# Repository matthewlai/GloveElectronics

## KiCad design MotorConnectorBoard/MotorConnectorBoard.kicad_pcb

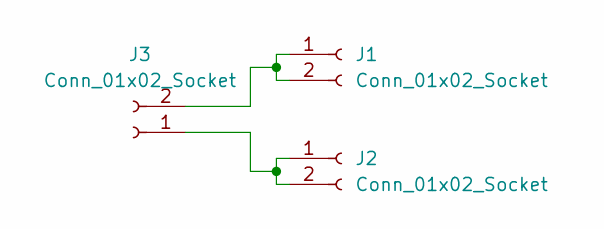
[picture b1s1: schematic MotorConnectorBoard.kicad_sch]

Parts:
J1, J2: Conn_01x02_Socket; PinHeader_1x02_P2.54mm_Vertical
J3: Conn_01x02_Socket; VLV101040A

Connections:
unnamed: J1.1, J1.2, J3.2
unnamed: J2.1, J2.2, J3.1

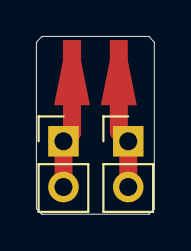
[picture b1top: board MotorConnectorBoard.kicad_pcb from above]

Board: 2 copper layers, 6.6 x 9.9 mm, 3 parts (0 on the bottom side), 2 nets.

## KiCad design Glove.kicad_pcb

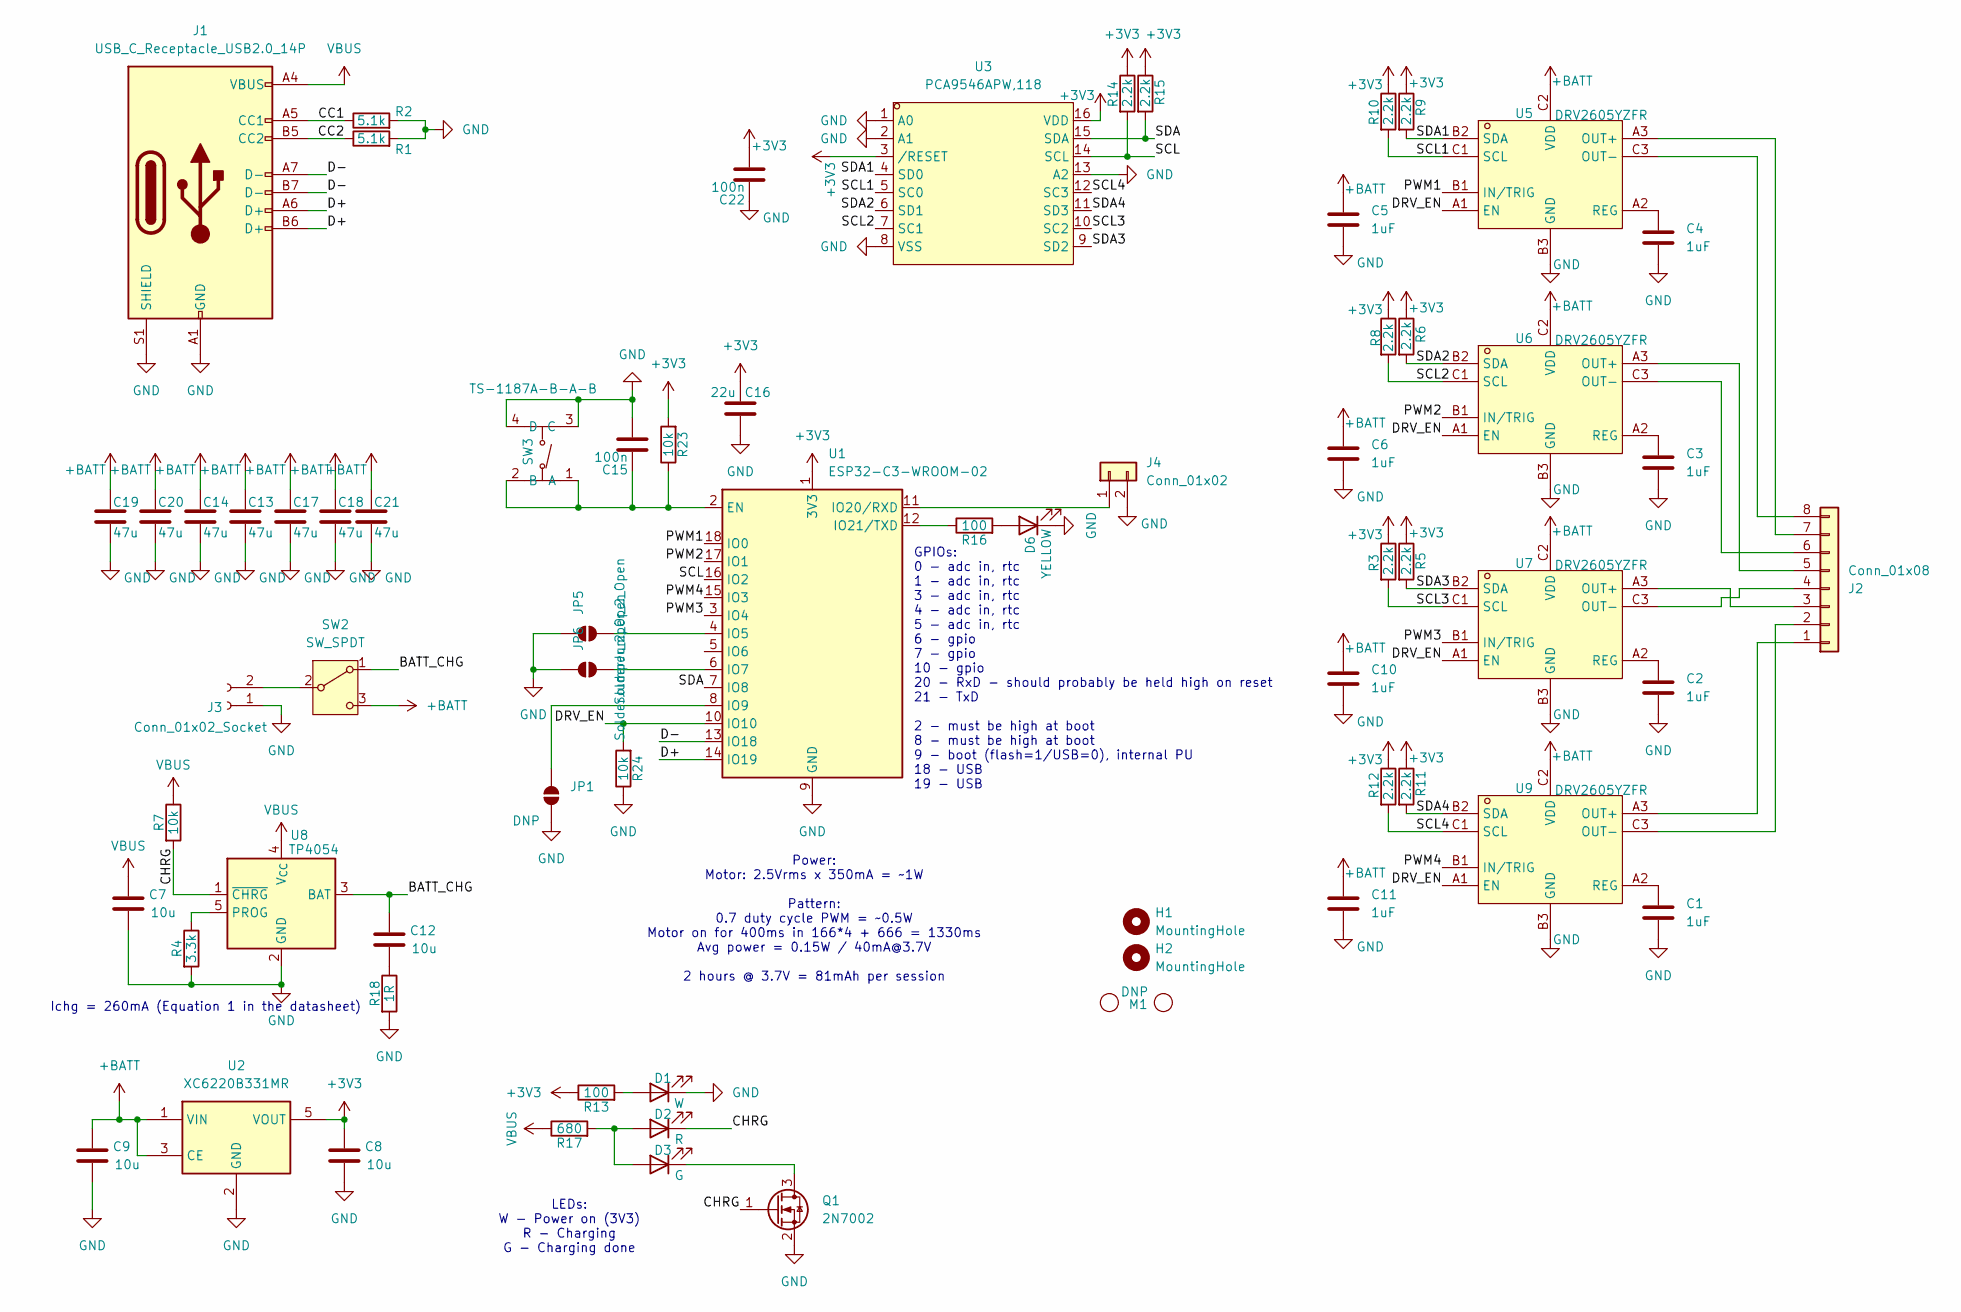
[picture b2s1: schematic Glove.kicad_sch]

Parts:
C1, C2, C3, C4, C5, C6, C10, C11: 1uF; C_0402_1005Metric; LCSC C52923
C7, C8, C9, C12: 10u; C_0603_1608Metric; LCSC C19702
C13, C14, C17, C18, C19, C20, C21: 47u; C_1206_3216Metric; LCSC C96123
C15, C22: 100n; C_0402_1005Metric; LCSC C1525
C16: 22u; C_0603_1608Metric; LCSC C59461
D1: W; LED_0603_1608Metric; LCSC C2290
D2: R; LED_0603_1608Metric; LCSC C2286
D3: G; LED_0603_1608Metric; LCSC C12624
D6: YELLOW; LED_0805_2012Metric; LCSC C2296
H1, H2: MountingHole; MountingHole_2.2mm_M2
J1: USB_C_Receptacle_USB2.0_14P; USB-C_SMD-TYPE-C-31-M-12; LCSC C165948
J2: Conn_01x08; PinHeader_2x04_P2.54mm_Vertical; LCSC C32713277
J3: Conn_01x02_Socket; CONN-SMD_B2B-PH-SM4-TB-LF-SN; LCSC C265003
J4: Conn_01x02; PinHeader_1x02_P2.54mm_Vertical
JP1: DNP; PinHeader_1x02_P2.54mm_Vertical
JP5, JP6: SolderJumper_2_Open; SolderJumper-2_P1.3mm_Open_RoundedPad1.0x1.5mm
M1: DNP; VLP2
Q1: 2N7002; SOT-323_SC-70; LCSC C7420322
R1, R2: 5.1k; R_0402_1005Metric; LCSC C25905
R3, R5, R6, R8, R9, R10, R11, R12, R14, R15: 2.2k; R_0402_1005Metric; LCSC C25879
R4: 3.3k; R_0402_1005Metric; LCSC C25890
R7, R23, R24: 10k; R_0402_1005Metric; LCSC C25744
R13, R16: 100; R_0402_1005Metric; LCSC C25076
R17: 680; R_0402_1005Metric; LCSC C25130
R18: 1R; R_0402_1005Metric; LCSC C25086
SW2: SW_SPDT; SW-TH_SK12D07VG3; LCSC C431547
SW3: TS-1187A-B-A-B; SW-SMD_4P-L5.1-W5.1-P3.70-LS6.5-TL_H1.5; LCSC Part C318884
U1: ESP32-C3-WROOM-02; LCSC C2934560
U2: XC6220B331MR; SOT-23-5; LCSC C86534
U3: PCA9546APW,118; SOP-16_L5.0-W4.4-P0.65-LS6.4-BL; LCSC Part C149507
U5, U6, U7, U9: DRV2605YZFR; DSBGA-9_L1.5-W1.5-R3-C3-P0.50-BL; LCSC Part C81079
U8: TP4054; SOT-23-5; LCSC C32574

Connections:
+3V3: C8.1, C16.1, C22.2, R3.1, R5.1, R6.1, R8.1, R9.1, R10.1, R11.1, R12.1, R13.1, R14.1, R15.1, R23.2, U1.1 (3V3), U2.5 (VOUT), U3.3 (/RESET), U3.16 (VDD)
+BATT: C5.1, C6.1, C9.1, C10.1, C11.1, C13.1, C14.1, C17.1, C18.1, C19.1, C20.1, C21.1, SW2.3 (C), U2.1 (VIN), U2.3 (CE), U5.C2 (VDD), U6.C2 (VDD), U7.C2 (VDD), U9.C2 (VDD)
/BATT_CHG: C12.1, SW2.1 (A), U8.3 (BAT)
/CC1: J1.A5 (CC1), R2.1
/CC2: J1.B5 (CC2), R1.1
/CHRG: D2.1 (K), Q1.1 (G), R7.2, U8.1 (~CHRG)
/D+: J1.A6 (D+), J1.B6 (D+), U1.14 (IO19)
/D-: J1.A7 (D-), J1.B7 (D-), U1.13 (IO18)
/DRV_EN: R24.2, U1.10 (IO10), U5.A1 (EN), U6.A1 (EN), U7.A1 (EN), U9.A1 (EN)
/PWM1: U1.18 (IO0), U5.B1 (IN/TRIG)
/PWM2: U1.17 (IO1), U6.B1 (IN/TRIG)
/PWM3: U1.3 (IO4), U7.B1 (IN/TRIG)
/PWM4: U1.15 (IO3), U9.B1 (IN/TRIG)
/SCL: R14.2, U1.16 (IO2), U3.14 (SCL)
/SCL1: R10.2, U3.5 (SC0), U5.C1 (SCL)
/SCL2: R8.2, U3.7 (SC1), U6.C1 (SCL)
/SCL3: R3.2, U3.10 (SC2), U7.C1 (SCL)
/SCL4: R12.2, U3.12 (SC3), U9.C1 (SCL)
/SDA: R15.2, U1.7 (IO8), U3.15 (SDA)
/SDA1: R9.2, U3.4 (SD0), U5.B2 (SDA)
/SDA2: R6.2, U3.6 (SD1), U6.B2 (SDA)
/SDA3: R5.2, U3.9 (SD2), U7.B2 (SDA)
/SDA4: R11.2, U3.11 (SD3), U9.B2 (SDA)
GND: C1.2, C2.2, C3.2, C4.2, C5.2, C6.2, C7.2, C8.2, C9.2, C10.2, C11.2, C13.2, C14.2, C15.2, C16.2, C17.2, C18.2, C19.2, C20.2, C21.2, C22.1, D1.1 (K), D6.1 (K), J1.A1 (GND), J1.A12 (GND), J1.B1 (GND), J1.B12 (GND), J1.S1 (SHIELD), J3.1, J4.2, JP1.1 (A), JP5.2 (B), JP6.2 (B), Q1.2 (S), R1.2, R2.2, R4.2, R18.2, R24.1, SW3.3 (C), SW3.4 (D), U1.9 (GND), U1.19 (GND), U2.2 (GND), U3.1 (A0), U3.2 (A1), U3.8 (VSS), U3.13 (A2), U5.B3 (GND), U6.B3 (GND), U7.B3 (GND), U8.2 (GND), U9.B3 (GND)
unnamed: C12.2, R18.1
unnamed: D1.2 (A), R13.2
unnamed: D2.2 (A), D3.2 (A), R17.2
unnamed: D3.1 (K), Q1.3 (D)
unnamed: D6.2 (A), R16.2
unnamed: J2.1, U9.A3 (OUT+)
unnamed: J2.2, U9.C3 (OUT-)
unnamed: J2.3, U7.A3 (OUT+)
unnamed: J2.4, U7.C3 (OUT-)
unnamed: J2.5, U6.A3 (OUT+)
unnamed: J2.6, U6.C3 (OUT-)
unnamed: J2.7, U5.A3 (OUT+)
unnamed: J2.8, U5.C3 (OUT-)
unnamed: J3.2, SW2.2 (B)
unnamed: J4.1, U1.11 (IO20/RXD)
unnamed: JP1.2 (B), U1.8 (IO9)
unnamed: JP5.1 (A), U1.4 (IO5)
unnamed: JP6.1 (A), U1.6 (IO7)
unnamed: C15.1, R23.1, SW3.1 (A), SW3.2 (B), U1.2 (EN)
unnamed: R16.1, U1.12 (IO21/TXD)
unnamed: C4.1, U5.A2 (REG)
unnamed: C3.1, U6.A2 (REG)
unnamed: C2.1, U7.A2 (REG)
unnamed: R4.1, U8.5 (PROG)
unnamed: C1.1, U9.A2 (REG)
VBUS: C7.1, J1.A4 (VBUS), J1.A9 (VBUS), J1.B4 (VBUS), J1.B9 (VBUS), R7.1, R17.1, U8.4 (V_{CC})

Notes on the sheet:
LEDs: W - Power on (3V3) R - Charging G - Charging done
GPIOs: 0 - adc in, rtc 1 - adc in, rtc 3 - adc in, rtc 4 - adc in, rtc 5 - adc in, rtc 6 - gpio 7 - gpio 10 - gpio 20 - RxD - should probably be held high on reset 21 - TxD 2 - must be high at boot 8 - must be high at boot 9 - boot (flash=1/USB=0), internal PU 18 - USB 19 - USB
Power: Motor: 2.5Vrms x 350mA = ~1W Pattern: 0.7 duty cycle PWM = ~0.5W Motor on for 400ms in 166*4 + 666 = 1330ms Avg power = 0.15W / 40mA@3.7V 2 hours @ 3.7V = 81mAh per session
Ichg = 260mA (Equation 1 in the datasheet)

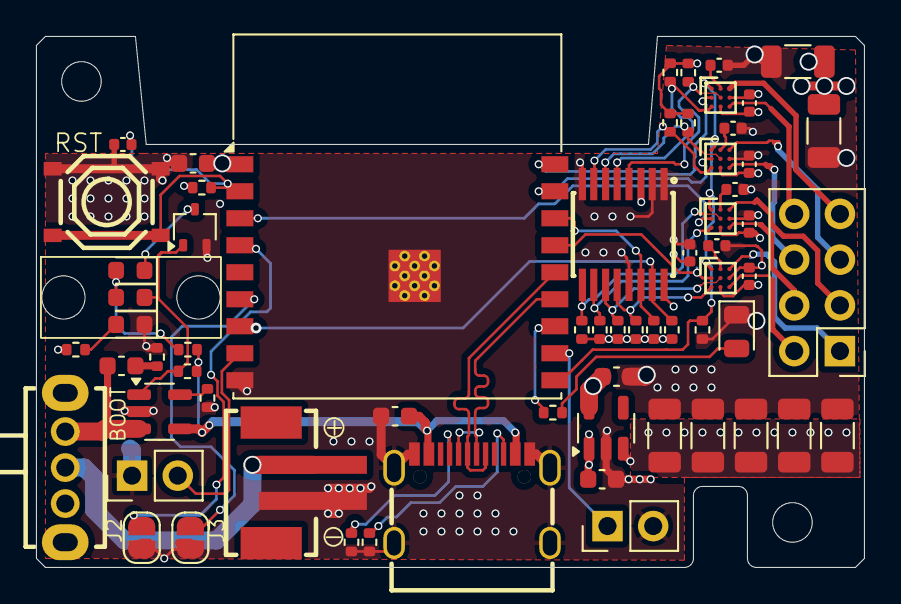
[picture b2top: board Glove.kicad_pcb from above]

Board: 4 copper layers, 46.0 x 29.5 mm, 67 parts (0 on the bottom side), 50 nets.

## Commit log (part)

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2025-05-25 Added button connector
2025-05-29 Firmware initial commit
2025-05-29 Fixed vibration frequency
2025-05-29 Optimised BLE params
2025-06-02 Update main.ino
    Refactored the loop into smaller bits. Still needs work, and to rely a lot less on Sleep() calls for timing.
    Also fixed Serial initialization, which was missing the baud rate.
2025-06-05 Fix immediate shutdown and lack of serial output
    * Fixed Serial initialization.
    * The battery low indication counter check was inverted.
2025-06-05 Pump up the power!
    Set the power to the motors to almost full. This is something that will ideally be configurable in the future.
2025-06-05 Readability improvements
    Group related functions , introduce a few constants, that kind of thing.
    Makes for a large change that doesn't do much in terms of code, unfortunately.
2025-06-08 Multi-threading implementation
    Separate BLE and motor control into separate threads.
    This seems to work more reliably. I don't think we're quite where we want in terms of synchronization, need to work out a way to make sure both gloves are on the same page about the pattern in a way 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
2025-06-09 Fix battery monitoring and memory leak
    Small improvements:
    Was reading the battery level only once.
    Was leaking memory on reconnect.
2025-06-10 Fix the client's cycle
    The client was calling RunMotors() twice per cycle, because the motor routine was ending before we got a new start of cycle.
    Fixed by waiting until the cycle's end after the motor routine is done.
    Also made the notification logging less noisy.
2025-06-13 Motor actuation skew measurement
    Abuse pin 20 (originally intended for an optional pushbutton we ended up not needing) to measure the time skew when activating the motors.
    This is not needed for operation, but it's useful during development to validate the effectiveness of clock skew correction.
